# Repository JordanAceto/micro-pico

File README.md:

# Micro-Pico tiny monosynth

## A lil' analog synth with:
- Two SSI2130 VCOs
    - sine, triangle, sawtooth, and pulse waves available
    - VCO B can by syncronized to VCO A (hard and soft sync available)
    - the VCOs share a single manual pulse width control
- Two minimoog style ADS envelope generators
    - These envelopes cycle through all four A, D, S, and R stages, but the Decay and Release stages share a single potentiometer
- Modulation LFO
    - triangle, square, and sample & hold waveforms
    - can be routed to VCO FM, PWM, or VCF modulation
    - `MOD CV` input controlls the LFO depth along with the LFO `LEVEL` knob, for mod-wheel antics
- Swappable VCF port
    - the VCF can be changed by plugging in a variety of [VCF plug-in boards](https://github.com/JordanAceto/VCF_plug_in_boards)
    - you need at least one of the above VCF boards to finish the synth
- Final linear VCA
    - simple linearized SSI2162 VCA
- Extra patch points on the pcb for mods and experimentation
    - independent aux FM inputs for the VCOs [-5v, +5v]
    - aux PWM CV [-5v, +5v]
    - aux VCF cutoff CV [-5v, +5v]
    - aux VCA amplitude CV [0v, +5v]
    - white noise out [-5v, +5v]
    - patch points for most of the important signals
- Powered with a standard guitar pedal style 9VDC center negative adapter
    - current draw is approximately 220mA **without** a VCF plug-in board installed
    - expect another 100mA or so depending on the VCF board used
    - so use a 9v adapter with at least 500mA capacity or greater

The feature set is quite limited. The emphasis is on small, simple, and all-analog signal path. A fun little jammer to hook up to a sequencer or CV keyboard.

## Construction notes:
- It is easier to install the trimpots, VCF port headers, and various through-hole parts before installing the pots and switches
    - you can still get to everything if you forget, or need to change something later
- When installing the front panel components
    - dry fit all of the pots, switches, and jacks before soldering
    - the rotary switches need a nut or spacer under the panel to match the height of the pots
    - the 9VDC connector needs a nut or spacer under the panel, and needs to be lifted off the board a little, so that it protrudes far enough to tighten the outer nut
    - tighten down all of the components, check for alighment and height issues, and only then start soldering
- The rotary switches need a sleeve adapter for the knobs to fit nicely
    - something like [this](https://www.amplifiedparts.com/products/potentiometer-adapter-sleeve-converts-6mm-or-18t-shaft-14)
    - or use a bit of tubing if you're DIY happy
- It's designed to fit in a Hammond 1590XX aluminum box
    - these are available pre-painted in a few colors
    - with a VCF plug-in board installed, the 1590XX is the *teensiest* bit too short, the trimpots hit the lid when tightened
        - you can put some 2mm-ish washers between the lid and the box
        - eventually I hope to make a gasket that adds a few mm height and looks cleaner
        - or it could even have an acrylic light plate like some people do with pedals
    - other chassis at least as big as the 1590XX (plus a few mm taller) could work

## Calibration:
- follow the [SSI2130 datasheet](https://www.soundsemiconductor.com/downloads/ssi2130datasheet.pdf) Tuning Process for the VCOs, or tune by ear
- calibrate the VCF according to the instructions on the main VCF plug-in board repo
- check that the white noise is about +/-5V in amplitude. You can try different BJTs or mess with the gain setting resistors, but as long as it's reasonably close the S&H setting will sound fine, it's not critical

## Status:
Safe to build!

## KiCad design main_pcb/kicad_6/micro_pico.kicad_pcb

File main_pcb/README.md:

# Main PCB for tiny monosynth

## [SCHEMATIC](https://github.com/JordanAceto/micro-pico/blob/main/main_pcb/docs/micro_pico-schematic.pdf)

Open `index.html` in a web browser for easy documentation navigation.

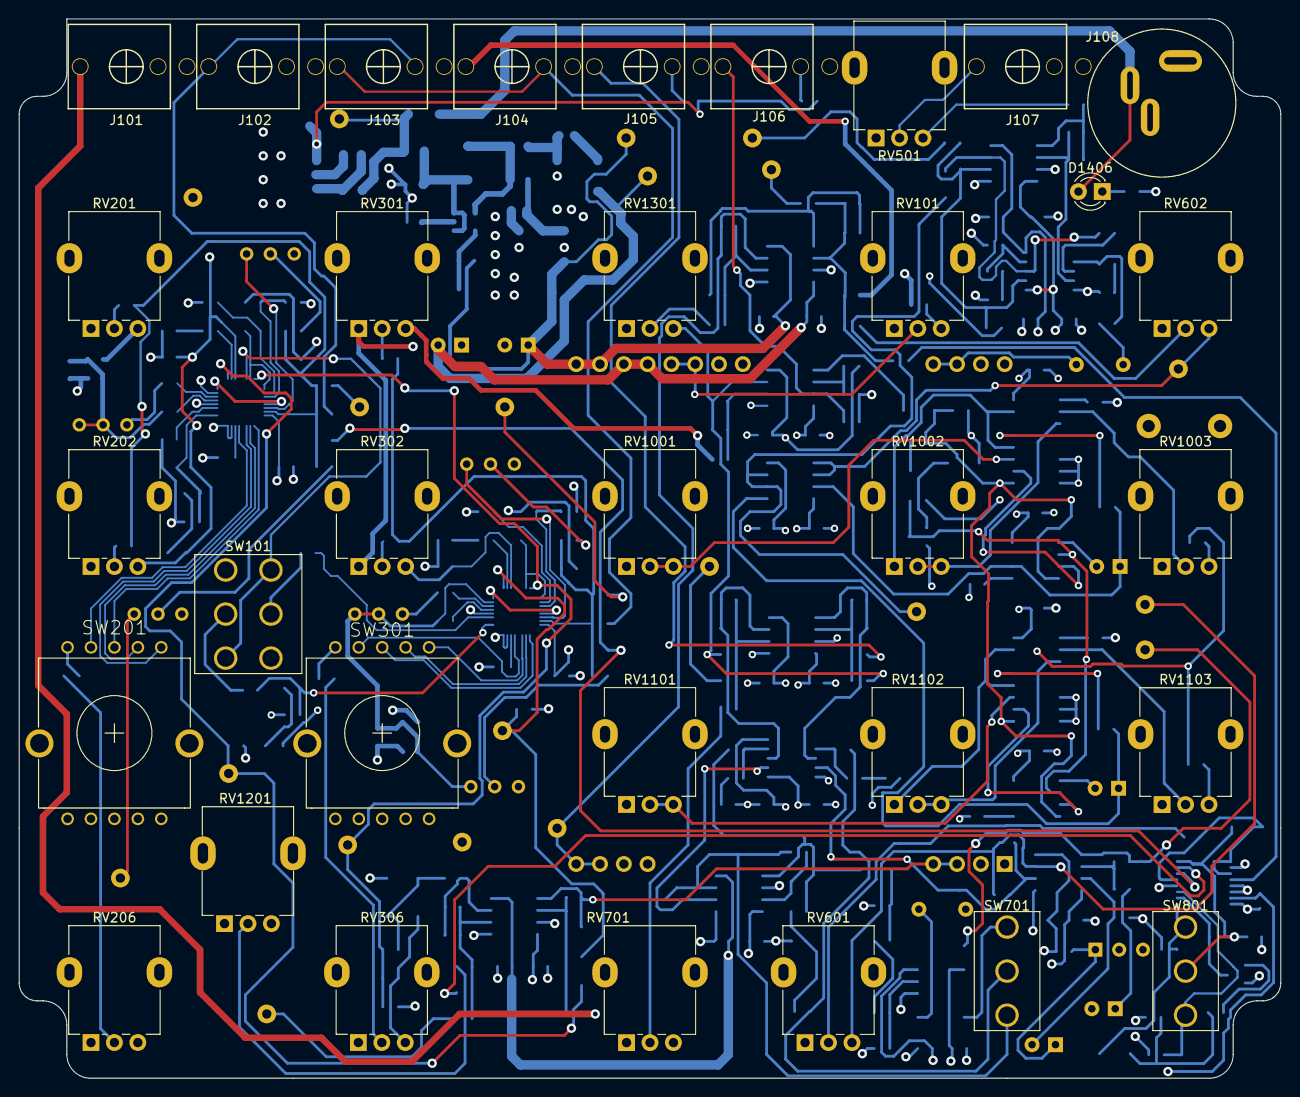
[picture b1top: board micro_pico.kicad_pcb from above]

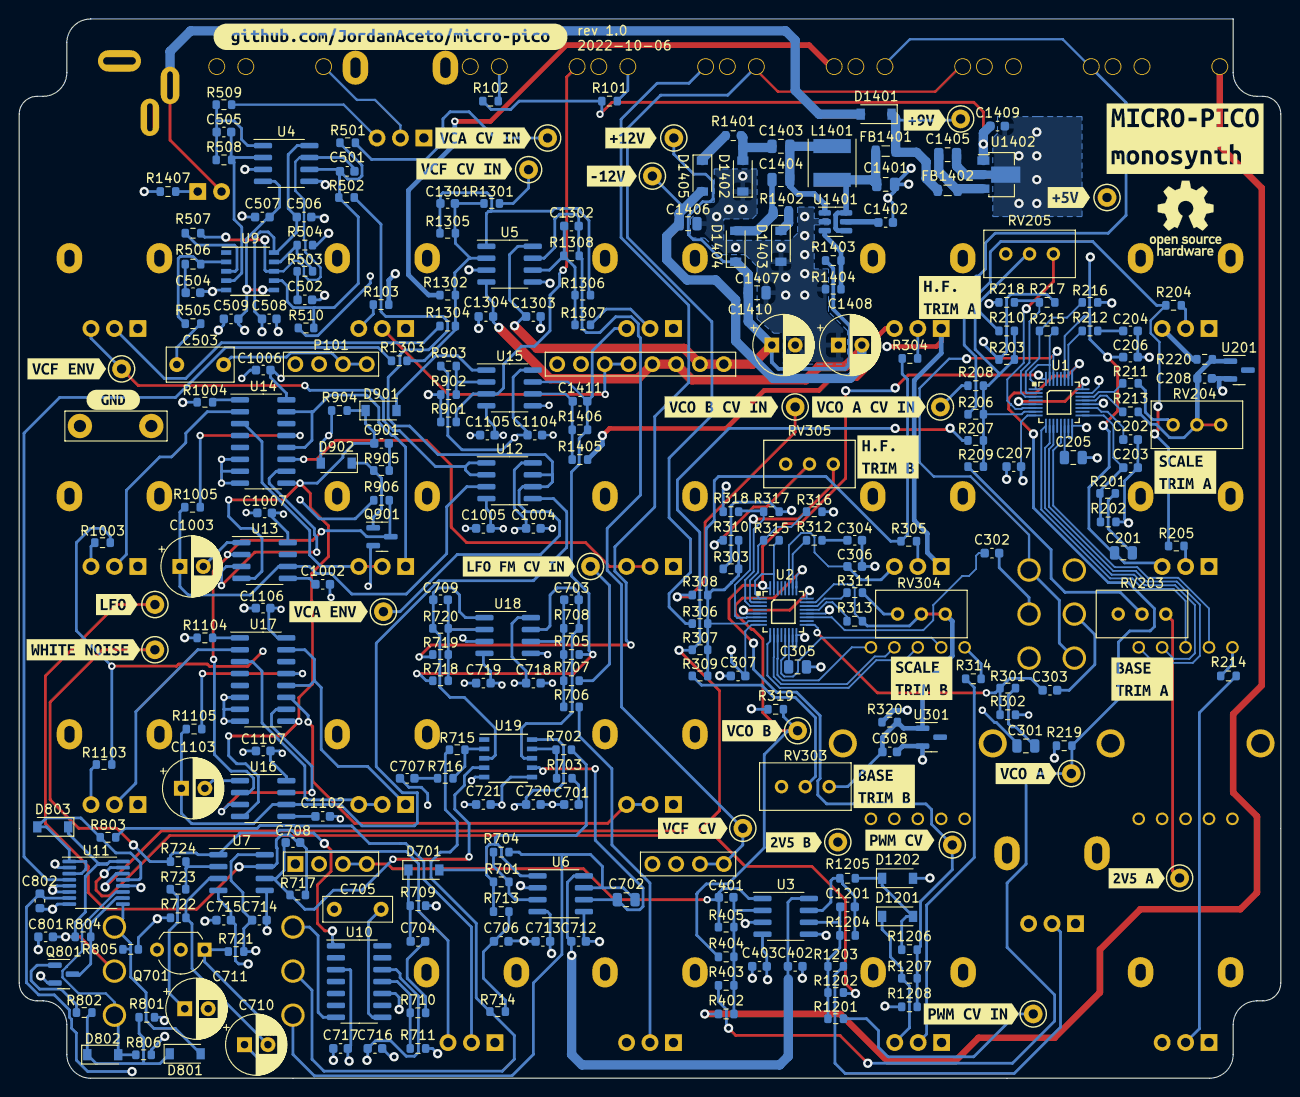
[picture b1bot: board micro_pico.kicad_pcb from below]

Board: 4 copper layers, 134.6 x 113.0 mm, 332 parts (299 on the bottom side), 182 nets.

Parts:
C201, C301: 10u; C_0805_2012Metric
C202, C203, C204, C302, C303, C304: 10n; C_0603_1608Metric
C205, C305: 3N9 COG; C_0805_2012Metric
C206, C207, C208, C306, C307, C308, C402, C403, C506, C507, C508, C509, C706, C712, C713, C714, C715, C716, C717, C718, C719, C720, C721, C801, C802, C1004, C1005, C1006, C1007, C1104, C1105, C1106, C1107, C1303, C1304, C1402, C1409, C1411: 100n; C_0603_1608Metric
C401, C505, C708, C901, C1302: 100p; C_0603_1608Metric
C501, C502, C504, C701, C703, C704, C707, C709, C1002, C1102, C1201, C1301: 1n; C_0603_1608Metric
C503: 470n; C_Rect_L7.0mm_W3.5mm_P5.00mm
C702: 10n; C_0805_2012Metric
C705: 2n2; C_Rect_L7.2mm_W2.5mm_P5.00mm_FKS2_FKP2_MKS2_MKP2
C710, C711, C1003, C1103, C1408, C1410: 10u; CP_Radial_D6.3mm_P2.50mm
C1401, C1406, C1407: 4u7; C_0805_2012Metric
C1403, C1404: 1u; C_0805_2012Metric
C1405: 470n; C_0805_2012Metric
D701, D801, D802, D803, D901, D902, D1201, D1202: 1N4148W; D_SOD-123
D1401, D1402, D1403, D1404, D1405: B5819W; D_SOD-123
D1406: XLMDK65D; LED_D3.0mm
FB1401, FB1402: 100R @ 100MHz; L_0805_2012Metric
J101, J102, J103, J104, J105, J106, J107: PJ301M-12
J108: PJ-011A; CUI_PJ-011A
J201, J301: aux_FM_in; TestPoint_Keystone_5000-5004_Miniature
J501: aux_AM_in; TestPoint_Keystone_5000-5004_Miniature
J701: white_noise; TestPoint_Keystone_5000-5004_Miniature
J702: aux_LFO_FM_in; TestPoint_Keystone_5000-5004_Miniature
J1201: aux_PWM_in; TestPoint_Keystone_5000-5004_Miniature
J1301: aux_VCF_FM_in; TestPoint_Keystone_5000-5004_Miniature
L1401: 10uH, 1.2A; L_Taiyo-Yuden_NR-50xx
P101: VCF_plug_in_port
Q701: 2N3904_wide; TO-92_Inline_Wide
Q801, Q901: MMBT3904; SOT-23
R101, R220, R320, R723, R803, R1205: 1k; R_0603_1608Metric
R102, R103, R201, R202, R301, R302, R709, R801, R802, R804, R805, R806, R904, R906, R1206, R1407: 10k; R_0603_1608Metric
R203, R303, R708: 39k; R_0603_1608Metric
R204, R304, R707: 200k; R_0603_1608Metric
R205, R305, R722: 2M2; R_0603_1608Metric
R206, R207, R208, R209, R214, R306, R307, R308, R309, R314, R402, R405, R501, R504, R704, R706, R715, R717, R718, R719, R901, R903, R905, R1301, R1302, R1303, R1306, R1308, R1405, R1406: 100k; R_0603_1608Metric
R210, R310: 270k; R_0603_1608Metric
R211, R311, R713, R714: 47k; R_0603_1608Metric
R212, R312, R503, R506, R509, R703, R716: 270; R_0603_1608Metric
R213, R313: 470k; R_0603_1608Metric
R215, R315: 3k9; R_0603_1608Metric
R216, R218, R316, R318, R507, R711: 4k7; R_0603_1608Metric
R217, R317, R508, R710, R902: 12k; R_0603_1608Metric
R219, R319: 18k; R_0603_1608Metric
R403, R404, R505: 27k; R_0603_1608Metric
R502, R721: 150k; R_0603_1608Metric
R510, R724: 10M; R_0603_1608Metric
R701, R1203, R1204, R1307: 220k; R_0603_1608Metric
R702, R1305: 22k; R_0603_1608Metric
R705: 68k; R_0603_1608Metric
R720, R1207, R1304: 56k; R_0603_1608Metric
R1003, R1103: 5k6; R_0603_1608Metric
R1004, R1005, R1104, R1105: 100; R_0603_1608Metric
R1201, R1202: 330k; R_0603_1608Metric
R1208: 6k8; R_0603_1608Metric
R1401, R1402: 1; R_0603_1608Metric
R1403: 114k; R_0603_1608Metric
R1404: 13k3; R_0603_1608Metric
RV101, RV206, RV306, RV1003, RV1103: 10k; Alpha_RD901F
RV201, RV202, RV301, RV302, RV601, RV602, RV701, RV1301: 100k; Alpha_RD901F
RV203, RV204, RV205, RV303, RV304, RV305: 5k; Potentiometer_Bourns_3296W_Vertical
RV501, RV1201: 5k; Bourns_PTV09
RV1001, RV1002, RV1101, RV1102: 1MA; Alpha_RD901F
SW101: SW_DP_on_on_on; DPDT_mini_toggle
SW201, SW301: SR1712F-0204; SR1712F_rotary_switch
SW701, SW801: SW_SPDT_CO; SPDT_mini_toggle
TP102: VCO_A; TestPoint_Keystone_5000-5004_Miniature
TP103: VCO_B; TestPoint_Keystone_5000-5004_Miniature
TP105: VCO_PWM_CV; TestPoint_Keystone_5000-5004_Miniature
TP106: VCF_FM_CV; TestPoint_Keystone_5000-5004_Miniature
TP201, TP301: 2V5; TestPoint_Keystone_5000-5004_Miniature
TP601: VCA_ENV; TestPoint_Keystone_5000-5004_Miniature
TP602: LFO; TestPoint_Keystone_5000-5004_Miniature
TP603: VCF_ENV; TestPoint_Keystone_5000-5004_Miniature
TP1401: +9; TestPoint_Keystone_5000-5004_Miniature
TP1402: -12; TestPoint_Keystone_5000-5004_Miniature
TP1403: +12; TestPoint_Keystone_5000-5004_Miniature
TP1404: +5; TestPoint_Keystone_5000-5004_Miniature
TP1407: GND; TestPoint_Bridge_Pitch7.62mm_Drill1.3mm
U1, U2: SSI2130; PQN32_HandSoldering
U3, U4, U5, U6, U7, U12, U15, U18: TL072; SOIC-8_3.9x4.9mm_P1.27mm
U9, U19: SSI2162; SSOP-10_3.9x4.9mm_P1.00mm
U10: LF398_SOIC14; SOIC-14_3.9x8.7mm_P1.27mm
U11: CD4053; TSSOP-16_4.4x5mm_P0.65mm
U13, U16: TLC555; SOIC-8_3.9x4.9mm_P1.27mm
U14, U17: CD4052B; SOIC-16_3.9x9.9mm_P1.27mm
U201, U301: LM4040C-2.5; SOT-23
U1401: LT3467A; TSOT-23-6
U1402: L78L05_SOT89; SOT-89-3
kibuzzard-62EC6A3A: G***; kibuzzard-62EC6A3A
kibuzzard-62EC6A5B: G***; kibuzzard-62EC6A5B
kibuzzard-62EC69EF: G***; kibuzzard-62EC69EF
kibuzzard-62EDACE7: G***; kibuzzard-62EDACE7
kibuzzard-62EDACF8: G***; kibuzzard-62EDACF8
kibuzzard-62EDADB4: G***; kibuzzard-62EDADB4
kibuzzard-62EE6A0D: G***; kibuzzard-62EE6A0D
kibuzzard-62EE6A9F: G***; kibuzzard-62EE6A9F
kibuzzard-62EE6AE1: G***; kibuzzard-62EE6AE1
kibuzzard-62EE6B39: G***; kibuzzard-62EE6B39
kibuzzard-62EE6BC1: G***; kibuzzard-62EE6BC1
kibuzzard-62EE6CF1: G***; kibuzzard-62EE6CF1
kibuzzard-62EE6D2D: G***; kibuzzard-62EE6D2D
kibuzzard-62EE6D7D: G***; kibuzzard-62EE6D7D
kibuzzard-62EE6D14: G***; kibuzzard-62EE6D14
kibuzzard-62EE6D53: G***; kibuzzard-62EE6D53
kibuzzard-62EE6DEE: G***; kibuzzard-62EE6DEE
kibuzzard-62EE6E32: G***; kibuzzard-62EE6E32
kibuzzard-62EE6FA2: G***; kibuzzard-62EE6FA2
kibuzzard-62EE64B9: G***; kibuzzard-62EE64B9
kibuzzard-62EE65B4: G***; kibuzzard-62EE65B4
kibuzzard-62EE69E1: G***; kibuzzard-62EE69E1
kibuzzard-62EE748D: G***; kibuzzard-62EE748D
kibuzzard-62EE7039: G***; kibuzzard-62EE7039
kibuzzard-62EE7070: G***; kibuzzard-62EE7070
kibuzzard-62FE2A23: G***; kibuzzard-62FE2A23
kibuzzard-633F7F05: G***; kibuzzard-633F7F05
kibuzzard-634019ED: G***; kibuzzard-634019ED
kibuzzard-634019F6: G***; kibuzzard-634019F6

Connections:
+5V: C201.2, C206.1, C301.2, C306.1, C801.1, C1409.1, D803.1 (K), D1201.1 (K), R101.2, R102.2, R103.1, R220.1, R320.1, R804.1, R1207.2, R1405.1, RV201.3, RV202.3, RV206.3, RV301.3, RV302.3, RV306.3, RV701.3, SW801.2, TP1404.1, U1.27 (V+), U2.27 (V+), U11.16 (VDD), U1402.1 (OUT)
+9V: D1401.1 (K), FB1401.1, FB1402.1, TP1401.1
+12V: C402.1, C506.1, C508.1, C712.1, C714.1, C716.1, C718.1, C720.1, C1004.1, C1006.1, C1007.1, C1104.1, C1106.1, C1107.1, C1303.1, C1407.1, C1410.1, D1404.1 (K), P101.9 (V+), P101.10 (V+), R721.1, R903.2, R906.1, R1003.1, R1103.1, R1403.2, RV1001.1, RV1101.1, TP1403.1, U3.8 (V+), U4.8 (V+), U5.8 (V+), U6.8 (V+), U7.8 (V+), U9.10 (V+), U10.12 (V+), U12.8 (V+), U13.8 (VCC), U14.16 (VDD), U15.8 (V+), U16.8 (VCC), U17.16 (VDD), U18.8 (V+), U19.10 (V+)
-5V_REF: C1411.2, R504.2, R510.2, R705.2, R718.2, R1406.2, RV201.1, RV202.1, RV301.1, RV302.1, RV1201.3, RV1301.3, U15.7
-12V: C207.2, C307.2, C403.2, C507.2, C509.2, C713.2, C715.2, C717.2, C719.2, C721.2, C802.2, C1005.2, C1105.2, C1304.2, C1406.2, C1408.2, D1405.2 (A), P101.11 (V-), P101.12 (V-), TP1402.1, U1.8 (V-), U2.8 (V-), U3.4 (V-), U4.4 (V-), U5.4 (V-), U6.4 (V-), U7.4 (V-), U9.6 (V-), U10.3 (V-), U11.7 (VEE), U12.4 (V-), U15.4 (V-), U18.4 (V-), U19.6 (V-)
/CV_generators/GATE_IN: J106.3, R901.1, U15.3 (+)
/CV_generators/LFO/HI_Z_SQUARE: R714.2, R715.2, SW701.2
/CV_generators/LFO/OUT: C708.1, R717.1, RV601.3, TP602.1, U7.7
/CV_generators/LFO/RAW_SQUARE: D701.2 (A), R701.2, R702.2, R713.1, U6.1
/CV_generators/LFO/S&H: SW701.3, U10.7
/CV_generators/LFO/TRIANGLE: C702.2, R704.2, SW701.1, U6.7
/CV_generators/LFO/WHITE_NOISE: J701.1, R724.2, U7.1, U10.1 (I)
/CV_generators/LFO_DEPTH_CV: J105.3, R719.2
/CV_generators/LFO_switching/LFO_IN: R803.1, RV601.2
/CV_generators/LFO_switching/LFO_TO_PWM: R1202.1, U11.15 (Y)
/CV_generators/LFO_switching/LFO_TO_VCF: R1303.1, U11.4 (Z)
/CV_generators/VCA_CV: R502.2, TP601.1, U12.6 (-), U12.7
/CV_generators/VCA_env/GATE: C901.1, D901.1 (K), R904.1, U13.4 (R), U14.9 (B), U16.4 (R), U17.9 (B)
/CV_generators/VCA_env/~TRIG: Q901.3 (C), R906.2, U13.2 (TR), U16.2 (TR)
/CV_generators/VCF_CV_IN: J104.3, R1302.1
/CV_generators/VCF_CV_scaler/VCF_ENV_IN: R1304.1, RV602.2
/CV_generators/VCF_FM_CV: C1302.2, P101.7 (F_CV_IN), P101.8 (F_CV_IN), R1308.2, TP106.1, U5.7
/CV_generators/VCF_env/OUT: RV602.3, TP603.1, U12.1, U12.2 (-)
/PWM_CV: R1206.2, R1207.1, R1208.2, TP105.1, U1.32 (pwm_in_+), U2.32 (pwm_in_+)
/RAW_9VDC: D1401.2 (A), D1406.2 (A), J108.2
/VCA/SIGNAL_IN: C503.1, P101.17 (SIG_OUT), P101.18 (SIG_OUT)
/VCA/SIGNAL_OUT: J107.3, RV501.2
/VCO_A/LOCAL_2V5_REF: C208.1, R203.2, R213.2, R217.2, R220.2, RV203.3, RV204.2, RV204.3, TP201.1, U1.23 (vref), U201.1 (K)
/VCO_A/SWITCHED_OUT: R219.2, R403.1, TP102.1, U1.25 (mix_out)
/VCO_A/V_PER_OCT_IN_1: J102.3, J103.2, R206.2
/VCO_A_PULSE: SW101.1 (A), SW101.6 (C), U1.30 (pulse_out)
/VCO_B/HARD_SYNC_IN: C303.2, SW101.2 (B)
/VCO_B/LOCAL_2V5_REF: C308.1, R303.2, R313.2, R317.2, R320.2, RV303.3, RV304.2, RV304.3, TP301.1, U2.23 (vref), U301.1 (K)
/VCO_B/SOFT_SYNC_IN: C302.2, SW101.5 (B)
/VCO_B/SWITCHED_OUT: R319.2, R404.1, TP103.1, U2.25 (mix_out)
/VCO_B/V_PER_OCT_IN_1: J103.3, J104.2, R306.2
/VCO_FM_CV: R207.2, R307.2, U11.14 (X)
/audio_mixer/EXT_AUDIO_IN: J101.3, R402.1
/audio_mixer/MIX_OUT: C401.2, P101.3 (SIG_IN), P101.4 (SIG_IN), R405.2, U3.1
GND: C202.2, C203.2, C204.2, C205.2, C206.2, C207.1, C208.2, C304.2, C305.2, C306.2, C307.1, C308.2, C402.2, C403.1, C502.2, C504.2, C506.2, C507.1, C508.2, C509.1, C701.2, C705.2, C706.2, C707.2, C711.2, C712.2, C713.1, C714.2, C715.1, C716.2, C717.1, C718.2, C719.1, C720.2, C721.1, C801.2, C802.1, C1002.2, C1003.2, C1004.2, C1005.1, C1006.2, C1007.2, C1102.2, C1103.2, C1104.2, C1105.1, C1106.2, C1107.2, C1303.2, C1304.1, C1401.2, C1402.2, C1405.2, C1406.1, C1407.2, C1408.1, C1409.2, C1410.2, D902.2 (A), D1202.2 (A), D1402.1 (K), D1403.2 (A), J101.1, J101.2, J102.1, J102.2, J103.1, J104.1, J105.1, J106.1, J107.1, J108.1, P101.1 (GND), P101.2 (GND), P101.5 (GND), P101.6 (GND), P101.15 (GND), P101.16 (GND), P101.19 (GND), P101.20 (GND), Q701.2 (B), Q801.2 (E), Q901.2 (E), R202.2, R216.1, R218.1, R219.1, R302.2, R316.1, R318.1, R319.1, R709.2, R711.2, R722.2, R801.2, R805.2, R806.2, R901.2, R902.1, R904.2, R1004.2, R1104.2, R1208.1, R1404.1, R1407.1, RV101.1, RV203.1, RV205.1, RV206.1, RV303.1, RV305.1, RV306.1, RV501.1, RV601.1, RV602.1, RV701.1, RV1003.1, RV1103.1, RV1201.1, RV1301.1, SW101.3 (C), SW101.4 (A), TP1407.1, U1.15 (dgnd), U1.16 (agnd), U1.20 (hft_base), U2.15 (dgnd), U2.16 (agnd), U2.20 (hft_base), U3.3 (+), U3.5 (+), U4.3 (+), U4.5 (+), U5.3 (+), U5.5 (+), U6.2 (-), U6.5 (+), U7.5 (+), U9.5 (GND), U10.10 (T), U11.2 (Y0), U11.5 (Z0), U11.6 (Inh), U11.8 (VSS), U11.12 (X0), U13.1 (GND), U14.6 (INH), U14.7 (VEE), U14.8 (VSS), U15.5 (+), U16.1 (GND), U17.6 (INH), U17.7 (VEE), U17.8 (VSS), U18.3 (+), U18.5 (+), U19.5 (GND), U201.2 (A), U301.2 (A), U1401.2 (GND), U1402.2 (GND)
unnamed: C201.1, R201.1
unnamed: C202.1, U1.19 (soft_sync)
unnamed: C203.1, R201.2, R202.1, U1.17 (hard_sync)
unnamed: C204.1, R212.2
unnamed: C205.1, U1.14 (tcap)
unnamed: C301.1, R301.1
unnamed: C302.1, U2.19 (soft_sync)
unnamed: C303.1, R301.2, R302.1, U2.17 (hard_sync)
unnamed: C304.1, R312.2
unnamed: C305.1, U2.14 (tcap)
unnamed: C401.1, R402.2, R403.2, R404.2, R405.1, U3.2 (-)
unnamed: C501.1, R507.1, U4.7, U9.8
unnamed: C501.2, R501.2, R502.1, R510.1, U4.6 (-), U9.7
unnamed: C502.1, R503.2
unnamed: C503.2, R505.2
unnamed: C504.1, R506.2
unnamed: C505.1, R508.1, R509.1, U4.1
unnamed: C505.2, R508.2, U4.2 (-), U9.4
unnamed: C701.1, R703.2
unnamed: C702.1, U6.6 (-), U19.7
unnamed: C703.1, R708.2, U18.7, U19.8
unnamed: C703.2, R705.1, R706.2, R707.1, R708.1, U18.6 (-)
unnamed: C704.1, D701.1 (K), R709.1
unnamed: C704.2, R710.1
unnamed: C705.1, U10.8 (Ch)
unnamed: C706.1, R713.2, R714.1
unnamed: C707.1, R716.2
unnamed: C708.2, R717.2, U7.6 (-), U19.4
unnamed: C709.1, R720.2, U18.1, U19.3
unnamed: C709.2, R718.1, R719.1, R720.1, U18.2 (-)
unnamed: C710.1, Q701.1 (E), R721.2
unnamed: C710.2, R722.1, U7.3 (+)
unnamed: C711.1, R723.2
unnamed: C901.2, R905.1
unnamed: C1002.1, U13.5 (CV)
unnamed: C1003.1, R1005.2, U12.3 (+), U13.6 (THR)
unnamed: C1102.1, U16.5 (CV)
unnamed: C1103.1, R1105.2, U12.5 (+), U16.6 (THR)
unnamed: C1201.1, R1201.2, R1202.2, R1203.2, R1204.1, U3.6 (-)
unnamed: C1201.2, R1204.2, R1205.1, U3.7
unnamed: C1301.1, R1301.2, R1302.2, R1303.2, R1304.2, R1305.1, U5.2 (-)
unnamed: C1301.2, R1305.2, R1306.1, U5.1
unnamed: C1302.1, R1306.2, R1307.2, R1308.1, U5.6 (-)
unnamed: C1401.1, FB1401.2, L1401.1, U1401.4 (~SHDN), U1401.6 (Vin)
unnamed: C1402.1, U1401.5 (SS)
unnamed: C1403.1, C1404.2, L1401.2, U1401.1 (SW)
unnamed: C1403.2, D1402.2 (A), R1401.1
unnamed: C1404.1, D1404.2 (A), R1402.2
unnamed: C1405.1, FB1402.2, U1402.3 (IN)
unnamed: C1411.1, R1405.2, R1406.1, U15.6 (-)
unnamed: D801.1 (K), D802.1 (K), R801.1, R802.1
unnamed: D801.2 (A), R805.1, SW801.3, U11.9 (C)
unnamed: D802.2 (A), R806.1, SW801.1, U11.11 (A)
unnamed: D803.2 (A), R803.2, U11.1 (Y1), U11.3 (Z1), U11.13 (X1)
unnamed: D901.2 (A), U15.1
unnamed: D902.1 (K), Q901.1 (B), R905.2
unnamed: D1201.2 (A), D1202.1 (K), R1205.2, R1206.1
unnamed: D1403.1 (K), R1402.1
unnamed: D1405.1 (K), R1401.2
unnamed: D1406.1 (K), R1407.2
unnamed: J105.2, R101.1
unnamed: J106.2, R102.1
unnamed: J201.1, R208.1
unnamed: J301.1, R308.1
unnamed: J501.1, R501.1
unnamed: J702.1, R707.2
unnamed: J1201.1, R1201.1
unnamed: J1301.1, R1301.1
unnamed: P101.13 (Q_CV_IN), P101.14 (Q_CV_IN), RV101.2
unnamed: Q801.1 (B), R802.2
unnamed: Q801.3 (C), R804.2, U11.10 (B)
unnamed: R103.2, RV101.3
unnamed: R203.1, R204.1, R205.1, R206.1, R207.1, R208.2, R209.1, R210.2, U1.7 (expo_freq)
unnamed: R204.2, RV201.2
unnamed: R205.2, RV202.2
unnamed: R209.2, RV203.2
unnamed: R210.1, RV205.2
unnamed: R211.1, RV204.1
unnamed: R211.2, U1.22 (expo_scale)
unnamed: R212.1, U1.26 (bw_comp)
unnamed: R213.1, U1.21 (lin_freq)
unnamed: R214.1, RV206.2
unnamed: R214.2, SW201.1
unnamed: R215.1, R216.2, U1.2 (sine_in_+)
unnamed: R215.2, U1.1 (tri_out), U1.31 (pwm_in_-)
unnamed: R217.1, R218.2, U1.3 (sine_in_-)
unnamed: R303.1, R304.1, R305.1, R306.1, R307.1, R308.2, R309.1, R310.2, U2.7 (expo_freq)
unnamed: R304.2, RV301.2
unnamed: R305.2, RV302.2
unnamed: R309.2, RV303.2
unnamed: R310.1, RV305.2
unnamed: R311.1, RV304.1
unnamed: R311.2, U2.22 (expo_scale)
unnamed: R312.1, U2.26 (bw_comp)
unnamed: R313.1, U2.21 (lin_freq)
unnamed: R314.1, RV306.2
unnamed: R314.2, SW301.1
unnamed: R315.1, R316.2, U2.2 (sine_in_+)
unnamed: R315.2, U2.1 (tri_out), U2.31 (pwm_in_-)
unnamed: R317.1, R318.2, U2.3 (sine_in_-)
unnamed: R503.1, R504.1, U9.9
unnamed: R505.1, R506.1, U9.2
unnamed: R507.2, U9.3
unnamed: R509.2, RV501.3
unnamed: R701.1, R704.1, U6.3 (+)
unnamed: R702.1, R703.1, U19.9
unnamed: R706.1, RV701.2
unnamed: R710.2, R711.1, U10.11 (Hold)
unnamed: R715.1, R716.1, U19.2
unnamed: R723.1, R724.1, U7.2 (-)
unnamed: R902.2, R903.1, U15.2 (-)
unnamed: R1003.2, RV1003.3
unnamed: R1004.1, U14.1 (Y0)
unnamed: R1005.1, U14.13 (X)
unnamed: R1103.2, RV1103.3
unnamed: R1104.1, U17.1 (Y0)
unnamed: R1105.1, U17.13 (X)
unnamed: R1203.1, RV1201.2
unnamed: R1307.1, RV1301.2
unnamed: R1403.1, R1404.2, U1401.3 (FB)
unnamed: RV205.3, U1.6 (hf_track)
unnamed: RV305.3, U2.6 (hf_track)
unnamed: RV1001.2, RV1001.3, U14.11 (X3)
unnamed: RV1002.1, U14.12 (X0), U14.15 (X2)
unnamed: RV1002.2, RV1002.3, U14.3 (Y)
unnamed: RV1003.2, U14.2 (Y2)
unnamed: RV1101.2, RV1101.3, U17.11 (X3)
unnamed: RV1102.1, U17.12 (X0), U17.15 (X2)
unnamed: RV1102.2, RV1102.3, U17.3 (Y)
unnamed: RV1103.2, U17.2 (Y2)
unnamed: SW201.2, U1.13 (aux_2_mix)
unnamed: SW201.3, U1.9 (tri_mix)
unnamed: SW201.4, U1.10 (saw_mix)
unnamed: SW201.5, U1.11 (pulse_mix)
unnamed: SW301.2, U2.13 (aux_2_mix)
unnamed: SW301.3, U2.9 (tri_mix)
unnamed: SW301.4, U2.10 (saw_mix)
unnamed: SW301.5, U2.11 (pulse_mix)
unnamed: U1.5 (aux_in_2), U1.24 (sine_out)
unnamed: U2.5 (aux_in_2), U2.24 (sine_out)
unnamed: U13.3 (Q), U14.10 (A)
unnamed: U16.3 (Q), U17.10 (A)

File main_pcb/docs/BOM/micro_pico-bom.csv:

Row,Description,Part,References,Value,Footprint,Quantity Per PCB,Status,Datasheet
1,Unpolarized capacitor,C,C401 C505 C708 C901 C1302,100p,C_0603_1608Metric,5, ,~
2,Unpolarized capacitor,C,C501 C502 C504 C701 C703 C704 C707 C709 C1002 C1102 C1201 C1301,1n,C_0603_1608Metric,12, ,~
3,Unpolarized capacitor,C,C705,2n2,C_Rect_L7.2mm_W2.5mm_P5.00mm_FKS2_FKP2_MKS2_MKP2,1, ,~
4,Unpolarized capacitor,C,C205 C305,3N9 COG,C_0805_2012Metric,2, ,~
5,Unpolarized capacitor,C,C202 C203 C204 C302 C303 C304,10n,C_0603_1608Metric,6, ,~
6,Unpolarized capacitor,C,C702,10n,C_0805_2012Metric,1, ,~
7,Unpolarized capacitor,C,C206 C207 C208 C306 C307 C308 C402 C403 C506 C507 C508 C509 C706 C712 C713 C714 C715 C716 C717 C718 C719 C720 C721 C801 C802 C1004 C1005 C1006 C1007 C1104 C1105 C1106 C1107 C1303 C1304 C1402 C1409 C1411,100n,C_0603_1608Metric,38, ,~
8,Unpolarized capacitor,C,C1405,470n,C_0805_2012Metric,1, ,~
9,Unpolarized capacitor,C,C503,470n,C_Rect_L7.0mm_W3.5mm_P5.00mm,1, ,~
10,Unpolarized capacitor,C,C1403 C1404,1u,C_0805_2012Metric,2, ,~
11,Unpolarized capacitor,C,C1401 C1406 C1407,4u7,C_0805_2012Metric,3, ,~
12,Polarized capacitor,C_Polarized,C710 C711 C1003 C1103 C1408 C1410,10u,CP_Radial_D6.3mm_P2.50mm,6, ,~
13,Unpolarized capacitor,C,C201 C301,10u,C_0805_2012Metric,2, ,~
14,"75V 0.15A Fast Switching Diode, SOD-123",1N4148W,D701 D801 D802 D803 D901 D902 D1201 D1202,1N4148W,D_SOD-123,8, ,https://www.vishay.com/docs/85748/1n4148w.pdf
15,Schottky diode,D_Schottky,D1401 D1402 D1403 D1404 D1405,B5819W,D_SOD-123,5, ,~
16,Light emitting diode,LED,D1406,XLMDK65D,LED_D3.0mm,1, ,~
17,"Ferrite bead, small symbol",FerriteBead_Small,FB1401 FB1402,100R @ 100MHz,L_0805_2012Metric,2, ,~
18,DC Barrel Jack with an internal switch,PJ-011A,J108,PJ-011A,CUI_PJ-011A,1, ,~
19,"Audio Jack, 2 Poles (Mono / TS), Switched T Pole (Normalling)",PJ301M-12,J101 J102 J103 J104 J105 J106 J107,PJ301M-12,PJ301M-12,7, ,~
20,Inductor symbol for simulation only,INDUCTOR,L1401,"10uH, 1.2A",L_Taiyo-Yuden_NR-50xx,1, ,~
21,,VCF_plug_in_port,P101,VCF_plug_in_port,VCF_plug_in_port,1, ,
22,"0.2A Ic, 40V Vce, Small Signal NPN Transistor, TO-92",2N3904_wide,Q701,2N3904_wide,TO-92_Inline_Wide,1, ,https://www.onsemi.com/pub/Collateral/2N3903-D.PDF
23,"0.2A Ic, 40V Vce, Small Signal NPN Transistor, SOT-23",MMBT3904,Q801 Q901,MMBT3904,SOT-23,2, ,https://www.onsemi.com/pub/Collateral/2N3903-D.PDF
24,Resistor,R,R1401 R1402,1,R_0603_1608Metric,2, ,~
25,Resistor,R,R1004 R1005 R1104 R1105,100,R_0603_1608Metric,4, ,~
26,Resistor,R,R212 R312 R503 R506 R509 R703 R716,270,R_0603_1608Metric,7, ,~
27,Resistor,R,R101 R220 R320 R723 R803 R1205,1k,R_0603_1608Metric,6, ,~
28,Resistor,R,R215 R315,3k9,R_0603_1608Metric,2, ,~
29,Resistor,R,R216 R218 R316 R318 R507 R711,4k7,R_0603_1608Metric,6, ,~
30,Resistor,R,R1003 R1103,5k6,R_0603_1608Metric,2, ,~
31,Resistor,R,R1208,6k8,R_0603_1608Metric,1, ,~
32,Resistor,R,R102 R103 R201 R202 R301 R302 R709 R801 R802 R804 R805 R806 R904 R906 R1206 R1407,10k,R_0603_1608Metric,16, ,~
33,Resistor,R,R217 R317 R508 R710 R902,12k,R_0603_1608Metric,5, ,~
34,Resistor,R,R1404,13k3,R_0603_1608Metric,1, ,~
35,Resistor,R,R219 R319,18k,R_0603_1608Metric,2, ,~
36,Resistor,R,R702 R1305,22k,R_0603_1608Metric,2, ,~
37,Resistor,R,R403 R404 R505,27k,R_0603_1608Metric,3, ,~
38,Resistor,R,R203 R303 R708,39k,R_0603_1608Metric,3, ,~
39,Resistor,R,R211 R311 R713 R714,47k,R_0603_1608Metric,4, ,~
40,Resistor,R,R720 R1207 R1304,56k,R_0603_1608Metric,3, ,~
41,Resistor,R,R705,68k,R_0603_1608Metric,1, ,~
42,Resistor,R,R206 R207 R208 R209 R214 R306 R307 R308 R309 R314 R402 R405 R501 R504 R704 R706 R715 R717 R718 R719 R901 R903 R905 R1301 R1302 R1303 R1306 R1308 R1405 R1406,100k,R_0603_1608Metric,30, ,~
43,Resistor,R,R1403,114k,R_0603_1608Metric,1, ,~
44,Resistor,R,R502 R721,150k,R_0603_1608Metric,2, ,~
45,Resistor,R,R204 R304 R707,200k,R_0603_1608Metric,3, ,~
46,Resistor,R,R701 R1203 R1204 R1307,220k,R_0603_1608Metric,4, ,~
47,Resistor,R,R210 R310,270k,R_0603_1608Metric,2, ,~
48,Resistor,R,R1201 R1202,330k,R_0603_1608Metric,2, ,~
49,Resistor,R,R213 R313,470k,R_0603_1608Metric,2, ,~
50,Resistor,R,R205 R305 R722,2M2,R_0603_1608Metric,3, ,~
51,Resistor,R,R510 R724,10M,R_0603_1608Metric,2, ,~
52,Potentiometer,R_Potentiometer,RV501 RV1201,5k,Bourns_PTV09,2, ,~
53,Trim-potentiometer,R_Potentiometer_Trim,RV203 RV204 RV205 RV303 RV304 RV305,5k,Potentiometer_Bourns_3296W_Vertical,6, ,~
54,Potentiometer,R_Potentiometer,RV101 RV206 RV306 RV1003 RV1103,10k,Alpha_RD901F,5, ,~
55,Potentiometer,R_Potentiometer,RV201 RV202 RV301 RV302 RV601 RV602 RV701 RV1301,100k,Alpha_RD901F,8, ,~
56,Potentiometer,R_Potentiometer,RV1001 RV1002 RV1101 RV1102,1MA,Alpha_RD901F,4, ,~
57,3 rotary switches with 4 positions,SR1712F-0204,SW201 SW301,SR1712F-0204,SR1712F_rotary_switch,2, ,
58,"Switch, dual pole double throw, separate symbols",SW_DP_on_on_on,SW101,SW_DP_on_on_on,DPDT_mini_toggle,1, ,~
59,"Switch, single pole double throw, center OFF position",SW_SPDT_MSM,SW701 SW801,SW_SPDT_CO,SPDT_mini_toggle,2, ,~
60,"CMOS double 4-channel analog multiplexer/demultiplexer, TSSOP-16/DIP-16/SOIC-16",CD4052B,U14 U17,CD4052B,SOIC-16_3.9x9.9mm_P1.27mm,2, ,http://www.ti.com/lit/ds/symlink/cd4052b.pdf
61,Triple analog Multiplexer 2 to 1 line,4053,U11,CD4053,TSSOP-16_4.4x5mm_P0.65mm,1, ,http://www.intersil.com/content/dam/Intersil/documents/cd40/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
62,"Positive 100mA 30V Linear Regulator, Fixed Output 5V, SOT-89",L78L05_SOT89,U1402,L78L05_SOT89,SOT-89-3,1, ,http://www.st.com/content/ccc/resource/technical/document/da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
63,"Sample And Hold Unity Gain Follower, SOIC-14",LF398_SOIC14,U10,LF398_SOIC14,SOIC-14_3.9x8.7mm_P1.27mm,1, ,http://www.ti.com/lit/ds/symlink/lf398-n.pdf
64,"2.500V Precision Micropower Shunt Voltage Reference, SOT-23",LM4040DBZ-2.5,U201 U301,LM4040C-2.5,SOT-23,2, ,http://www.ti.com/lit/ds/symlink/lm4040-n.pdf
65,,LT3467A,U1401,LT3467A,TSOT-23-6,1, ,
66,,SSI2130,U1 U2,SSI2130,PQN32_HandSoldering,2, ,
67,,SSI2162,U9 U19,SSI2162,SSOP-10_3.9x4.9mm_P1.00mm,2, ,https://www.soundsemiconductor.com/downloads/ssi2162datasheet.pdf
68,"Dual Low-Noise JFET-Input Operational Amplifiers, DIP-8/SOIC-8",TL072,U3 U4 U5 U6 U7 U12 U15 U18,TL072,SOIC-8_3.9x4.9mm_P1.27mm,8, ,http://www.ti.com/lit/ds/symlink/tl071.pdf
69,"Timer, 555 compatible, SOIC-8",LM555xM,U13 U16,TLC555,SOIC-8_3.9x4.9mm_P1.27mm,2, ,





Project info:
Schematic:,micro_pico
Variant:,default
Revision:,1.0
Date:,2022-10-06
KiCad Version:,6.0.5+dfsg-1~bpo11+1
Statistics:
Component Groups:,69
Component Count:,282 (221 SMD/ 48 THT)
Fitted Components:,282 (221 SMD/ 48 THT)
Number of PCBs:,1
Total Components:,282

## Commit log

2022-08-18 Fix schematic link
2022-08-19 Clarify ADSR description in README
2022-08-24 Update README, note about current status of files
2022-09-09 Update rev 0.1, fix VCA tails, add local 2v5 regs, change some pot footprints
2022-09-09 Update README after some rev 0.1 fixes.
2022-09-17 Change 555 timer type, fixes odd ADSR behavior
2023-01-21 Add mod-wheel VCA, fix occasional VCO freq locking
2023-01-21 Fix cropped SVG drill guide
2023-01-21 SVG drill guide fix round 2

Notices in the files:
main_pcb/kicad_6/micro_pico.kicad_pcb:
creativecommons.org/licences/by/4.0
Licence: CC by 4.0
